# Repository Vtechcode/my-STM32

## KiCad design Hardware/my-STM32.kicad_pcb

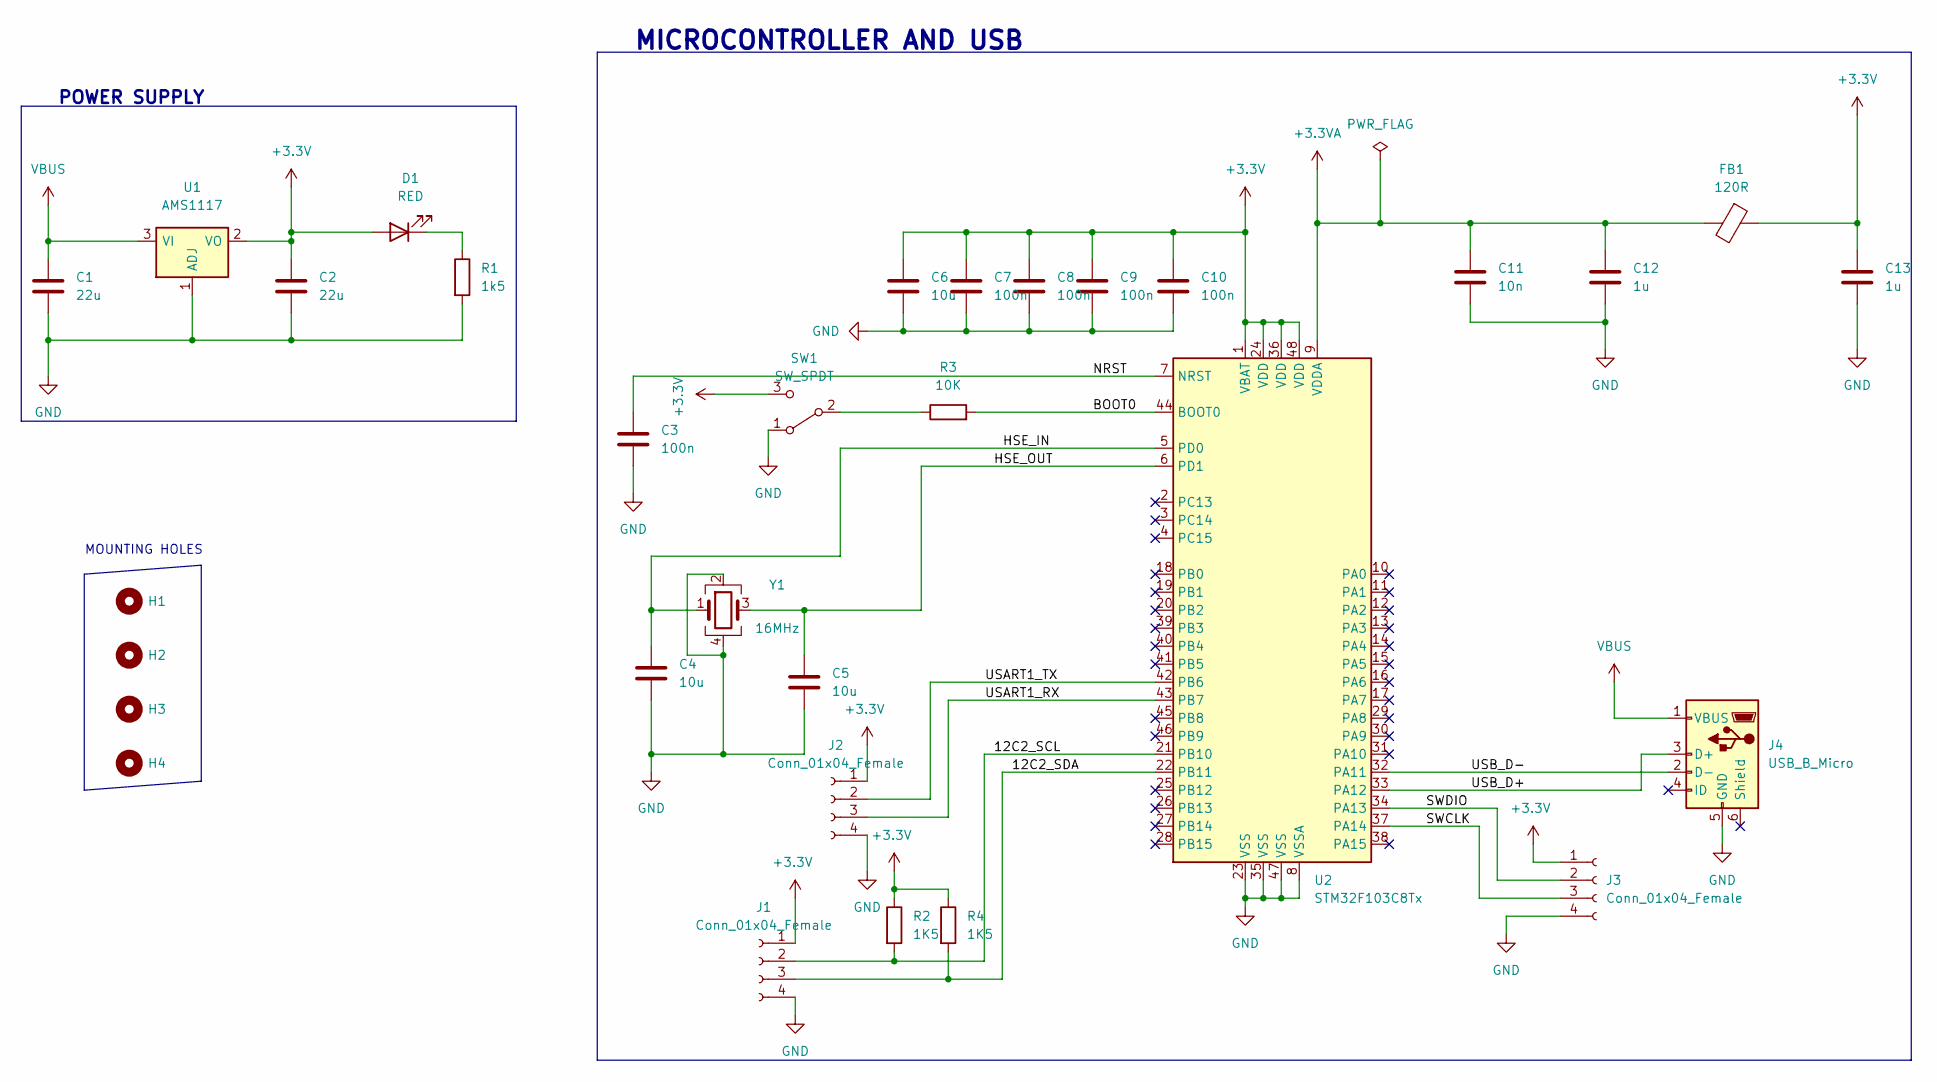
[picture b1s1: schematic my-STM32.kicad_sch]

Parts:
C1, C2: 22u; C_0402_1005Metric
C3, C7, C8, C9, C10: 100n; C_0805_2012Metric_Pad1.18x1.45mm_HandSolder
C4, C5, C6: 10u; C_0402_1005Metric_Pad0.74x0.62mm_HandSolder
C11: 10n; C_0805_2012Metric_Pad1.18x1.45mm_HandSolder
C12, C13: 1u; C_0805_2012Metric_Pad1.18x1.45mm_HandSolder
D1: RED; LED_0402_1005Metric_Pad0.77x0.64mm_HandSolder
FB1: 120R; L_0201_0603Metric_Pad0.64x0.40mm_HandSolder
H1, H2, H3, H4: MountingHole; MountingHole_2.1mm
J1, J2, J3: Conn_01x04_Female; PinHeader_1x04_P2.54mm_Vertical
J4: USB_B_Micro; USB_Micro-B_Molex-105133-0031
R1: 1k5; R_0402_1005Metric_Pad0.72x0.64mm_HandSolder
R2, R4: 1K5; R_0402_1005Metric_Pad0.72x0.64mm_HandSolder
R3: 10K; R_0805_2012Metric_Pad1.20x1.40mm_HandSolder
SW1: SW_SPDT; SW_SPDT_PCM12
U1: AMS1117; SOT-223-3_TabPin2
U2: STM32F103C8Tx; LQFP-48_7x7mm_P0.5mm
Y1: 16MHz; Crystal_SMD_0603-4Pin_6.0x3.5mm

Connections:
+3.3V: C2.1, C6.1, C7.1, C8.1, C9.1, C10.1, C13.1, D1.2 (A), FB1.1, J1.1, J2.1, J3.1, R2.1, R4.1, SW1.3 (C), U1.2 (VO), U2.1 (VBAT), U2.24 (VDD), U2.36 (VDD), U2.48 (VDD)
+3.3VA: C11.1, C12.1, FB1.2, U2.9 (VDDA)
/12C2_SCL: J1.2, R2.2, U2.21 (PB10)
/12C2_SDA: J1.3, R4.2, U2.22 (PB11)
/BOOT0: R3.2, U2.44 (BOOT0)
/HSE_IN: C4.1, U2.5 (PD0), Y1.1
/HSE_OUT: C5.1, U2.6 (PD1), Y1.3
/NRST: C3.1, U2.7 (NRST)
/SWCLK: J3.3, U2.37 (PA14)
/SWDIO: J3.2, U2.34 (PA13)
/USART1_RX: J2.3, U2.43 (PB7)
/USART1_TX: J2.2, U2.42 (PB6)
/USB_D+: J4.3 (D+), U2.33 (PA12)
/USB_D-: J4.2 (D-), U2.32 (PA11)
GND: C1.2, C2.2, C3.2, C4.2, C5.2, C6.2, C7.2, C8.2, C9.2, C10.2, C11.2, C12.2, C13.2, J1.4, J2.4, J3.4, J4.5 (GND), R1.2, SW1.1 (A), U1.1 (ADJ), U2.8 (VSSA), U2.23 (VSS), U2.35 (VSS), U2.47 (VSS), Y1.2, Y1.4
unnamed: D1.1 (K), R1.1
unnamed: R3.1, SW1.2 (B)
VBUS: C1.1, J4.1 (VBUS), U1.3 (VI)

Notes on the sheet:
MOUNTING HOLES
POWER SUPPLY
MICROCONTROLLER AND USB

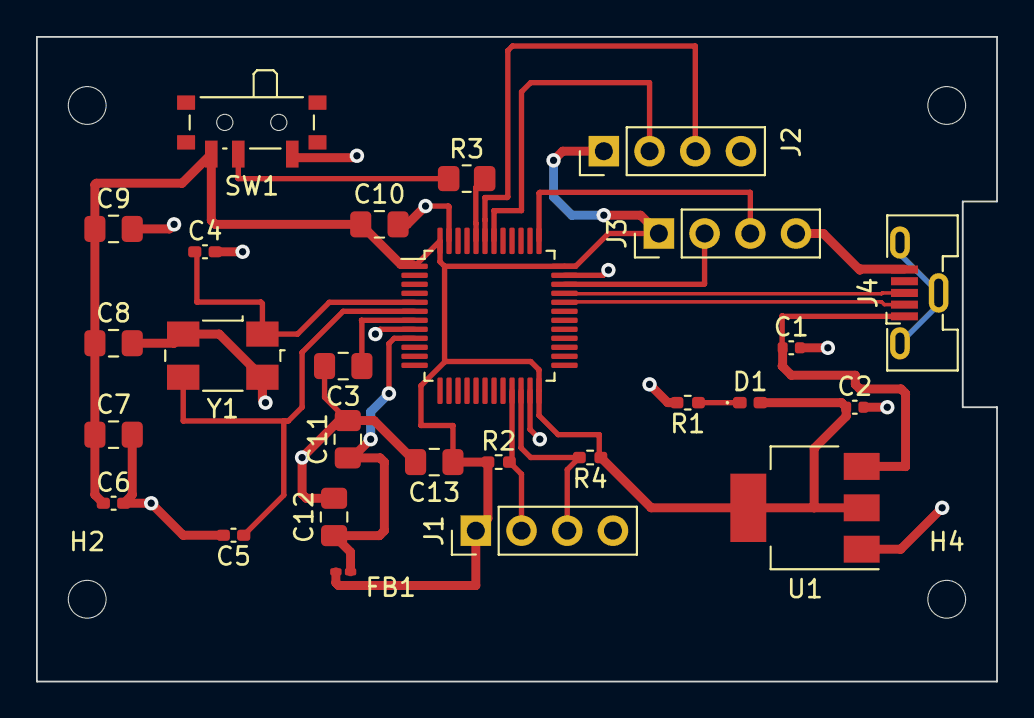
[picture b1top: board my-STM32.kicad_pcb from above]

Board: 2 copper layers, 53.3 x 35.8 mm, 31 parts (0 on the bottom side), 18 nets.

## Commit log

2023-10-02 Completed upto Routing
